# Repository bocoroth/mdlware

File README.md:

# mdlware
OSHW projects

This repo contains my OSHW (Open Source Hardware) projects, generally created using LTSpice (for sims) and KiCad (for board layout). These projects are mostly related to Eurorack synthesizers.

These projects are released under the CERN-OHL-2.0-S license, which means they are free for anyone to use or make derivatives thereof, provided derivatives remain open source (i.e., no proprietary derivatives). See the LICENSE file for more information.

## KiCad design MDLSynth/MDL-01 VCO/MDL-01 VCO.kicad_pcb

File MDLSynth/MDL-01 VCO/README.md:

# MDL-01 VCO

A tracking Voltage Controlled Oscillator

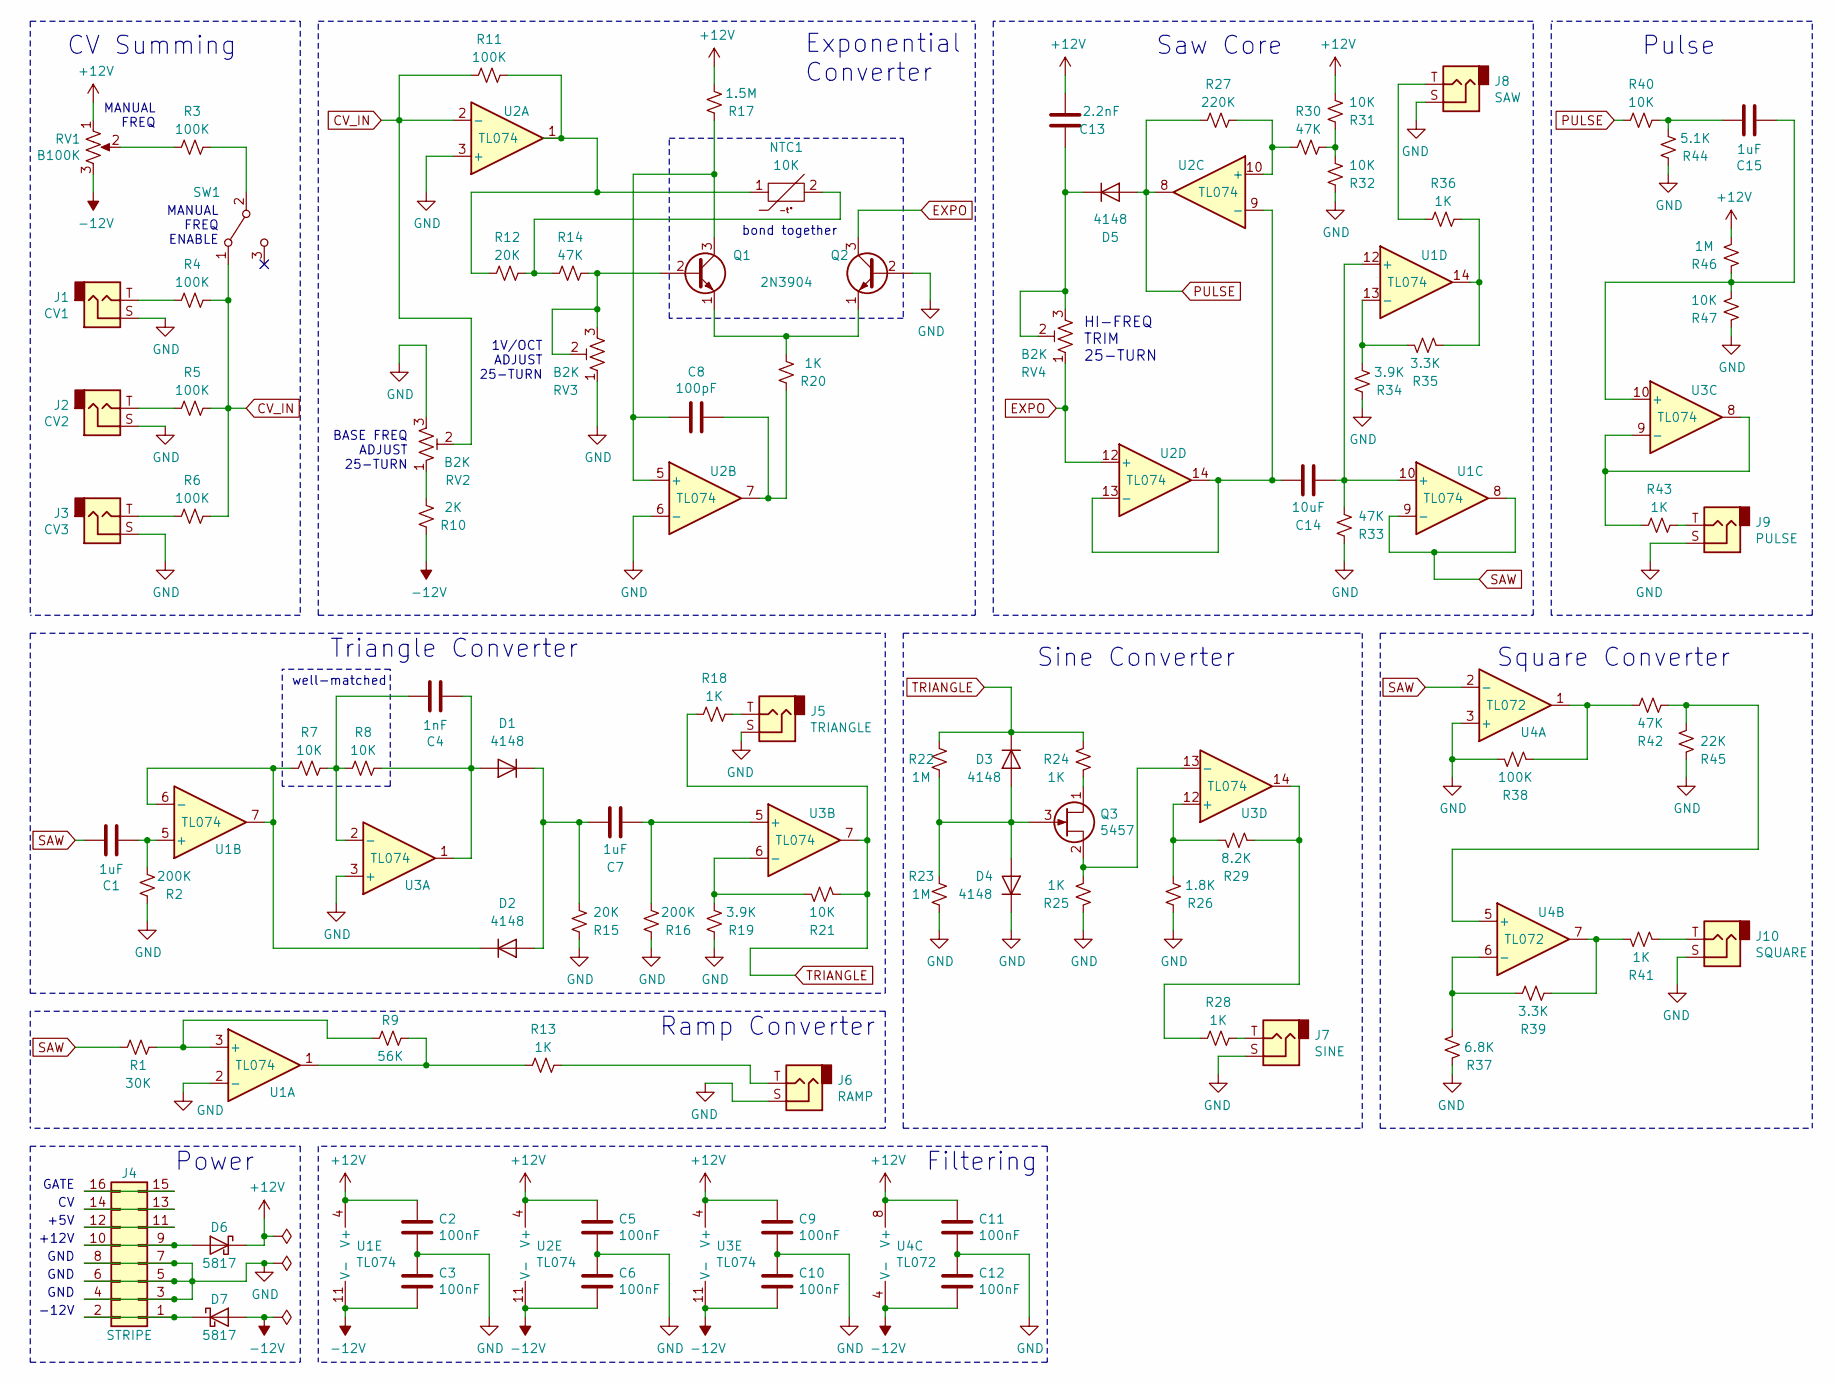
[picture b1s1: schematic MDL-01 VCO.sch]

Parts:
C1, C7, C15: 1uF; C_Elec_4x5.4; Digi-Key PCE4301CT-ND
C2, C3, C5, C6, C9, C10, C11, C12: 100nF; C_0805_2012Metric; Digi-Key 1276-2449-1-ND
C4: 1nF; C_0805_2012Metric; Digi-Key 1276-1020-1-ND
C8: 100pF; C_0805_2012Metric; Digi-Key 399-15000-1-ND
C13: 2.2nF; C_0805_2012Metric; Digi-Key 1276-2484-1-ND
C14: 10uF; C_Elec_6.3x5.4; Digi-Key PCE4294CT-ND
D1, D2, D3, D4, D5: 4148; D_MiniMELF; Digi-Key FDLL4148-D87ZCT-ND
D6, D7: 5817; D_SOD-323_HandSoldering; Digi-Key B5817WS-TPMSCT-ND
J1: CV1; Thonkiconn; Digi-Key --
J2: CV2; Thonkiconn; Digi-Key --
J3: CV3; Thonkiconn; Digi-Key --
J4: STRIPE; IDC-Header_2x08_P2.54mm_Vertical; Digi-Key S9171-ND
J5: TRIANGLE; Thonkiconn; Digi-Key --
J6: RAMP; Thonkiconn; Digi-Key --
J7: SINE; Thonkiconn; Digi-Key --
J8: SAW; Thonkiconn; Digi-Key --
J9: PULSE; Thonkiconn; Digi-Key --
J10: SQUARE; Thonkiconn; Digi-Key --
NTC1: 10K; THERM_NXRT15WB333JA1B010; Digi-Key 490-7171-ND
Q1, Q2: 2N3904; TO-92; Digi-Key 2N3904-APCT-ND
Q3: 5457; SOT-23; Digi-Key MMBF5457CT-ND
R1: 30K; R_0805_2012Metric; Digi-Key 2019-RK73H2ATTD3002FCT-ND
R2, R16: 200K; R_0805_2012Metric; Digi-Key 2019-RK73H2ATTD2003FCT-ND
R3, R4, R5, R6, R11, R38: 100K; R_0805_2012Metric; Digi-Key 13-AC0805FR-7W100KLCT-ND
R7, R8, R21, R31, R32, R40, R47: 10K; R_0805_2012Metric; Digi-Key 2019-RK73H2ATTE1002FCT-ND
R9: 56K; R_0805_2012Metric; Digi-Key 2019-RK73H2ATTD5602FCT-ND
R10: 2K; R_0805_2012Metric; Digi-Key RNCP0805FTD2K00CT-ND
R12, R15: 20K; R_0805_2012Metric; Digi-Key 2019-RK73H2ATTD2002FCT-ND
R13, R18, R20, R24, R25, R28, R36, R41, R43: 1K; R_0805_2012Metric; Digi-Key 2019-RK73H2ATTD1001FCT-ND
R14, R30, R33, R42: 47K; R_0805_2012Metric; Digi-Key 2019-RK73H2ATTD4702FCT-ND
R17: 1.5M; R_0805_2012Metric; Digi-Key 2019-RK73H2ATTD1504FCT-ND
R19, R34: 3.9K; R_0805_2012Metric; Digi-Key 2019-RK73H2ATTD3901FCT-ND
R22, R23, R46: 1M; R_0805_2012Metric; Digi-Key 2019-RK73H2ATTD1004FCT-ND
R26: 1.8K; R_0805_2012Metric; Digi-Key 2019-RK73H2ATTD1801FCT-ND
R27: 220K; R_0805_2012Metric; Digi-Key RHM220KAECT-ND
R29: 8.2K; R_0805_2012Metric; Digi-Key 2019-RK73H2ATTD8201FCT-ND
R35, R39: 3.3K; R_0805_2012Metric; Digi-Key 2019-RK73H2ATTD3R30FCT-ND
R37: 6.8K; R_0805_2012Metric; Digi-Key 2019-RK73H2ATTD6801FCT-ND
R44: 5.1K; R_0805_2012Metric; Digi-Key 2019-RK73H2ATTD5101FCT-ND
R45: 22K; R_0805_2012Metric; Digi-Key 2019-RK73H2ATTD2202FCT-ND
RV1: B100K; Potentiometer_Alpha_RD901F-40-00D_Single_Vertical; Digi-Key --
RV2, RV3, RV4: B2K; Potentiometer_Bourns_3296W_Vertical; Digi-Key 490-2880-ND
SW1: MANUAL FREQ; SW_Toggle_Blue_wSlots; Digi-Key EG2350-ND
U1, U2, U3: TL074; SOIC-14_3.9x8.7mm_P1.27mm; Digi-Key 296-TL074HIDRCT-ND
U4: TL072; SOIC-8_3.9x4.9mm_P1.27mm; Digi-Key 296-52761-1-ND

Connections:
+12V: C2.1, C5.1, C9.1, C11.1, C13.1, D6.1 (K), R17.2, R31.2, R46.2, RV1.1, U1.4 (V+), U2.4 (V+), U3.4 (V+), U4.8 (V+)
-12V: C3.2, C6.2, C10.2, C12.2, D7.2 (A), R10.1, RV1.3, U1.11 (V-), U2.11 (V-), U3.11 (V-), U4.4 (V-)
CV_IN: R4.1, R5.1, R6.1, R11.2, RV2.2, SW1.1 (A), U2.2 (-)
EXPO: Q2.3 (C), RV4.1, U2.12 (+)
GND: C2.2, C3.1, C5.2, C6.1, C9.2, C10.1, C11.2, C12.1, D4.1 (K), J1.S, J2.S, J3.S, J4.3, J4.4, J4.5, J4.6, J4.7, J4.8, J5.S, J6.S, J7.S, J8.S, J9.S, J10.S, Q2.2 (B), R2.1, R15.1, R16.1, R19.1, R23.1, R25.1, R26.1, R32.1, R33.1, R34.1, R37.2, R38.1, R44.1, R45.2, R47.1, RV2.3, RV3.1, U1.2 (-), U2.3 (+), U2.6 (-), U3.3 (+), U4.3 (+)
unnamed: C1.2, R2.2, U1.5 (+)
unnamed: C4.1, R7.1, R8.2, U3.2 (-)
unnamed: C4.2, D1.2 (A), R8.1, U3.1
unnamed: C7.1, D1.1 (K), D2.2 (A), R15.2
unnamed: C7.2, R16.2, U3.5 (+)
unnamed: C8.1, Q1.3 (C), R17.1, U2.5 (+)
unnamed: C8.2, R20.1, U2.7
unnamed: C13.2, D5.1 (K), RV4.2, RV4.3
unnamed: C14.1, U2.9 (-), U2.13 (-), U2.14
unnamed: C14.2, R33.2, U1.10 (+), U1.12 (+)
unnamed: C15.1, R40.1, R44.2
unnamed: C15.2, R46.1, R47.2, U3.10 (+)
unnamed: D2.1 (K), R7.2, U1.6 (-), U1.7
unnamed: D3.2 (A), D4.2 (A), Q3.3 (G), R22.1, R23.2
unnamed: D6.2 (A), J4.9, J4.10
unnamed: D7.1 (K), J4.1, J4.2
unnamed: J1.T, R4.2
unnamed: J2.T, R5.2
unnamed: J3.T, R6.2
unnamed: J4.11, J4.12
unnamed: J4.13, J4.14
unnamed: J4.15, J4.16
unnamed: J5.T, R18.1
unnamed: J6.T, R13.1
unnamed: J7.T, R28.1
unnamed: J8.T, R36.2
unnamed: J9.T, R43.1
unnamed: J10.T, R41.1
unnamed: NTC1.1, R11.1, R12.2, U2.1
unnamed: NTC1.2, R12.1, R14.2
unnamed: Q1.1 (E), Q2.1 (E), R20.2
unnamed: Q1.2 (B), R14.1, RV3.2, RV3.3
unnamed: Q3.1 (D), R24.1
unnamed: Q3.2 (S), R25.2, U3.13 (-)
unnamed: R1.1, R9.2, U1.3 (+)
unnamed: R3.1, SW1.2 (B)
unnamed: R3.2, RV1.2
unnamed: R10.2, RV2.1
unnamed: R9.1, R13.2, U1.1
unnamed: R19.2, R21.2, U3.6 (-)
unnamed: R26.2, R29.2, U3.12 (+)
unnamed: R27.1, R30.2, U2.10 (+)
unnamed: R28.2, R29.1, U3.14
unnamed: R30.1, R31.1, R32.2
unnamed: R34.2, R35.2, U1.13 (-)
unnamed: R35.1, R36.1, U1.14
unnamed: R37.1, R39.1, U4.6 (-)
unnamed: R38.2, R42.1, U4.1
unnamed: R39.2, R41.2, U4.7
unnamed: R42.2, R45.1, U4.5 (+)
unnamed: R43.2, U3.8, U3.9 (-)
PULSE: D5.2 (A), R27.2, R40.2, U2.8
SAW: C1.1, R1.2, U1.8, U1.9 (-), U4.2 (-)
TRIANGLE: D3.1 (K), R18.2, R21.1, R22.2, R24.2, U3.7

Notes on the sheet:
MANUAL FREQ
bond together
1V/OCT ADJUST 25-TURN
MANUAL FREQ ENABLE
CV Summing
Exponential Converter
Saw Core
HI-FREQ TRIM 25-TURN
Triangle Converter
Square Converter
Filtering
Ramp Converter
+5V
GATE
+12V
GND
-12V
BASE FREQ ADJUST 25-TURN
Pulse
well-matched
Sine Converter
Power

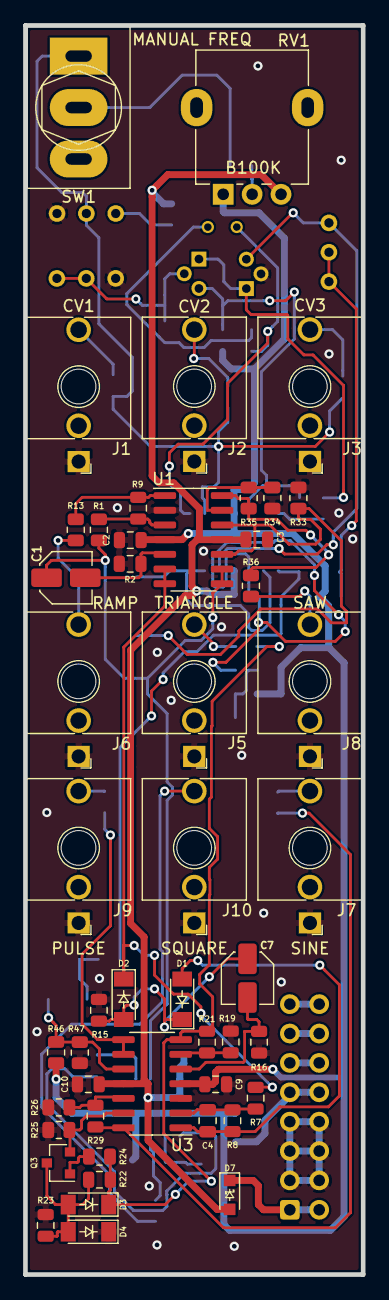
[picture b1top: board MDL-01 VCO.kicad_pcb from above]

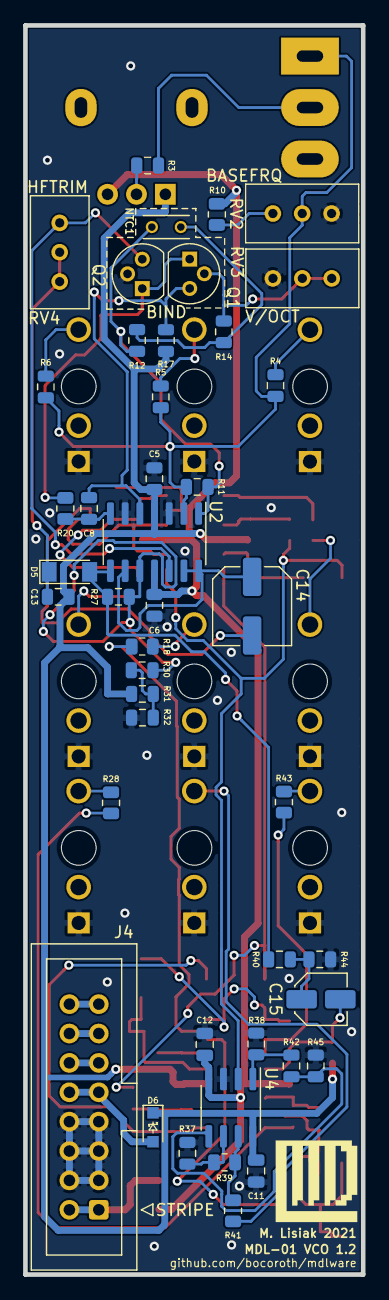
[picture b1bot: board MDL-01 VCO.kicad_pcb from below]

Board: 2 copper layers, 29.2 x 108.0 mm, 92 parts (44 on the bottom side), 59 nets.

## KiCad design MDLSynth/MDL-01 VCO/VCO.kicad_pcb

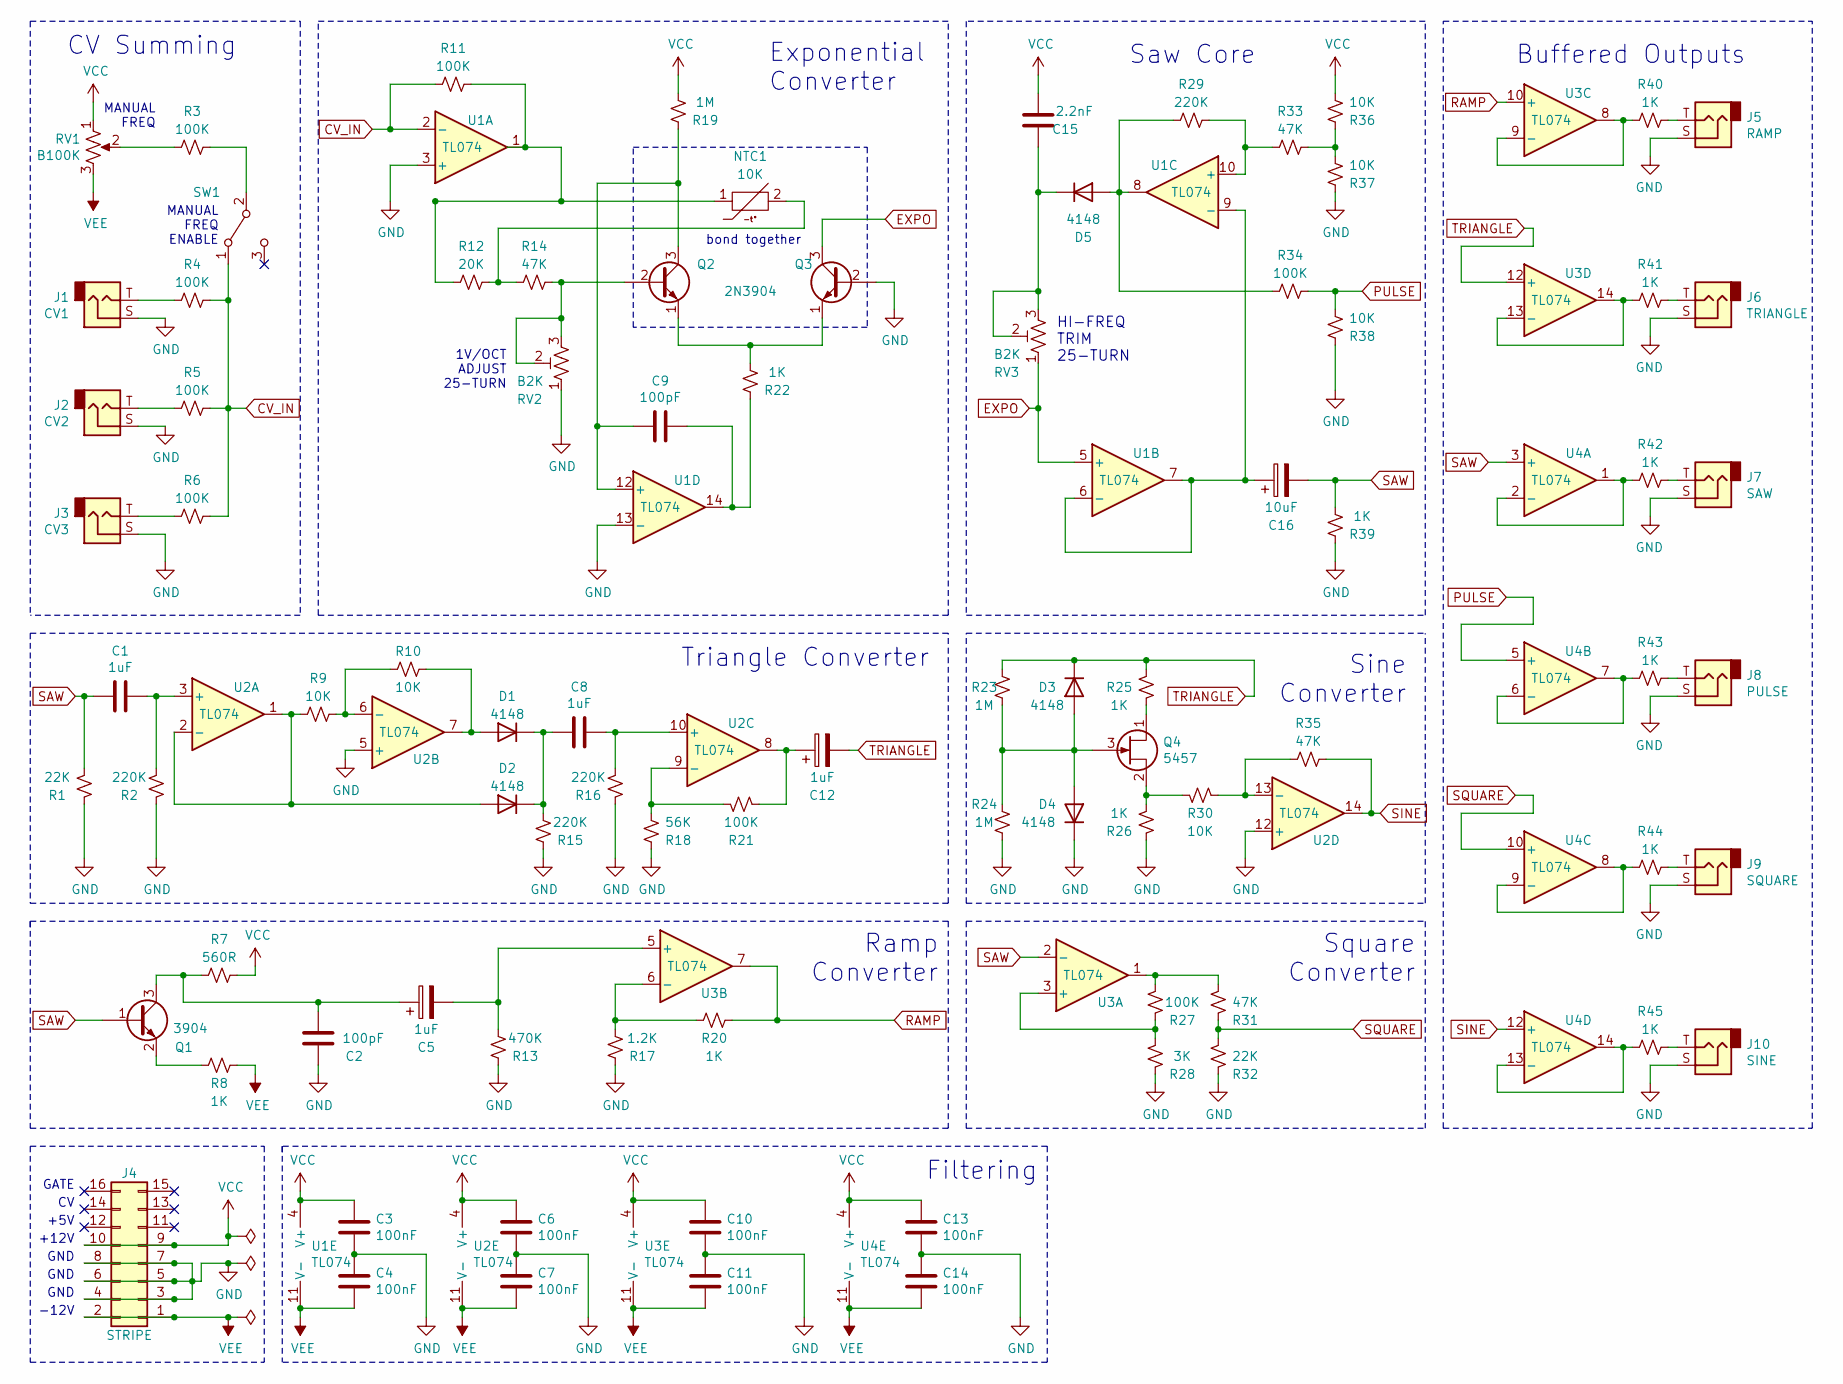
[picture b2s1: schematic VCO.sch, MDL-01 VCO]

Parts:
C1, C8: 1uF; C_1206_3216Metric; DIGIKEY 1276-3091-1-ND
C2, C9: 100pF; C_0805_2012Metric; DIGIKEY 1276-1014-1-ND
C3, C4, C6, C7, C10, C11, C13, C14: 100nF; C_0805_2012Metric; DIGIKEY 1276-1003-1-ND
C5, C12: 1uF; CP_Elec_4x5.4; DIGIKEY 732-8541-1-ND
C15: 2.2nF; C_0805_2012Metric; DIGIKEY 1276-1171-1-ND
C16: 10uF; CP_Elec_5x5.4; DIGIKEY 732-8451-1-ND
D1, D2, D3, D4, D5: 4148; D_MiniMELF; DIGIKEY FDLL4148CT-ND
J1: CV1; Thonkiconn; DIGIKEY --
J2: CV2; Thonkiconn; DIGIKEY --
J3: CV3; Thonkiconn; DIGIKEY --
J4: STRIPE; IDC-Header_2x08_P2.54mm_Vertical; DIGIKEY ED10523-ND
J5: RAMP; Thonkiconn; DIGIKEY --
J6: TRIANGLE; Thonkiconn; DIGIKEY --
J7: SAW; Thonkiconn; DIGIKEY --
J8: PULSE; Thonkiconn; DIGIKEY --
J9: SQUARE; Thonkiconn; DIGIKEY --
J10: SINE; Thonkiconn; DIGIKEY --
NTC1: 10K; THERM_NXRT15WB333JA1B010; DIGIKEY 490-18143-1-ND
Q1: 3904; SOT-23; DIGIKEY MMBT3904TPMSCT-ND
Q2, Q3: 2N3904; TO-92; DIGIKEY 2N3904D26ZCT-ND
Q4: 5457; SOT-23; DIGIKEY MMBF5457CT-ND
R1, R32: 22K; R_0805_2012Metric; DIGIKEY RMCF0805FT22K0CT-ND
R2, R15, R16, R29: 220K; R_0805_2012Metric; DIGIKEY RMCF0805FT220KCT-ND
R3, R4, R5, R6, R11, R21, R27, R34: 100K; R_0805_2012Metric; DIGIKEY RMCF0805FT100KCT-ND
R7: 560R; R_1206_3216Metric; DIGIKEY RMCF1206JT560RCT-ND
R8, R20, R22, R25, R26, R39, R40, R41, R42, R43, R44, R45: 1K; R_1206_3216Metric; DIGIKEY RMCF1206FT1K00CT-ND
R9, R10, R30, R36, R37, R38: 10K; R_0805_2012Metric; DIGIKEY RMCF0805FT10K0CT-ND
R12: 20K; R_0805_2012Metric; DIGIKEY RMCF0805FT20K0CT-ND
R13: 470K; R_0805_2012Metric; DIGIKEY 738-RMCF0805FT470KCT-ND
R14, R31, R33, R35: 47K; R_0805_2012Metric; DIGIKEY RMCF0805FT47K0CT-ND
R17: 1.2K; R_0805_2012Metric; DIGIKEY RMCF0805FT1K20CT-ND
R18: 56K; R_0805_2012Metric; DIGIKEY RMCF0805FT56K0CT-ND
R19, R23, R24: 1M; R_0805_2012Metric; DIGIKEY RMCF0805FG1M00CT-ND
R28: 3K; R_0805_2012Metric; DIGIKEY RMCF0805FT3K00CT-ND
RV1: B100K; Potentiometer_Alpha_RD901F-40-00D_Single_Vertical; DIGIKEY --
RV2, RV3: B2K; Potentiometer_Bourns_3296W_Vertical; DIGIKEY PV36W202C01B00
SW1: MANUAL FREQ; SW_Toggle_Blue_wSlots; DIGIKEY EG2350-ND
U1, U2: TL074; SOIC-14_3.9x8.7mm_P1.27mm; DIGIKEY 296-1283-1-ND
U3, U4: TL074; SOIC-14_3.9x8.7mm_P1.27mm; DIGIKEY 296-1282-1-ND

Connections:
CV_IN: R4.1, R5.1, R6.1, R11.2, SW1.1 (A), U1.2 (-)
EXPO: Q3.3 (C), RV3.1, U1.5 (+)
GND: C2.2, C3.2, C4.1, C6.2, C7.1, C10.2, C11.1, C13.2, C14.1, D4.1 (K), J1.S, J2.S, J3.S, J4.3, J4.4, J4.5, J4.6, J4.7, J4.8, J5.S, J6.S, J7.S, J8.S, J9.S, J10.S, Q3.2 (B), R1.1, R2.1, R13.1, R15.1, R16.1, R17.1, R18.1, R24.1, R26.1, R28.2, R32.2, R37.1, R38.1, R39.1, RV2.1, U1.3 (+), U1.13 (-), U2.5 (+), U2.12 (+)
unnamed: C1.2, R2.2, U2.3 (+)
unnamed: C2.1, C5.1, Q1.3 (C), R7.2
unnamed: C5.2, R13.2, U3.5 (+)
unnamed: C8.1, D1.1 (K), D2.1 (K), R15.2
unnamed: C8.2, R16.2, U2.10 (+)
unnamed: C9.1, Q2.3 (C), R19.1, U1.12 (+)
unnamed: C9.2, R22.1, U1.14
unnamed: C12.1, R21.1, U2.8
unnamed: C15.2, D5.1 (K), RV3.2, RV3.3
unnamed: C16.1, U1.6 (-), U1.7, U1.9 (-)
unnamed: D1.2 (A), R10.1, U2.7
unnamed: D2.2 (A), R9.2, U2.1, U2.2 (-)
unnamed: D3.2 (A), D4.2 (A), Q4.3 (G), R23.1, R24.2
unnamed: D5.2 (A), R29.2, R34.2, U1.8
unnamed: J1.T, R4.2
unnamed: J2.T, R5.2
unnamed: J3.T, R6.2
unnamed: J5.T, R40.1
unnamed: J6.T, R41.1
unnamed: J7.T, R42.1
unnamed: J8.T, R43.1
unnamed: J9.T, R44.1
unnamed: J10.T, R45.1
unnamed: NTC1.1, R11.1, R12.2, U1.1
unnamed: NTC1.2, R12.1, R14.2
unnamed: Q1.2 (E), R8.2
unnamed: Q2.1 (E), Q3.1 (E), R22.2
unnamed: Q2.2 (B), R14.1, RV2.2, RV2.3
unnamed: Q4.1 (D), R25.1
unnamed: Q4.2 (S), R26.2, R30.2
unnamed: R3.1, SW1.2 (B)
unnamed: R3.2, RV1.2
unnamed: R9.1, R10.2, U2.6 (-)
unnamed: R17.2, R20.2, U3.6 (-)
unnamed: R18.2, R21.2, U2.9 (-)
unnamed: R27.1, R31.1, U3.1
unnamed: R27.2, R28.1, U3.3 (+)
unnamed: R29.1, R33.2, U1.10 (+)
unnamed: R30.1, R35.2, U2.13 (-)
unnamed: R33.1, R36.1, R37.2
unnamed: R40.2, U3.8, U3.9 (-)
unnamed: R41.2, U3.13 (-), U3.14
unnamed: R42.2, U4.1, U4.2 (-)
unnamed: R43.2, U4.6 (-), U4.7
unnamed: R44.2, U4.8, U4.9 (-)
unnamed: R45.2, U4.13 (-), U4.14
PULSE: R34.1, R38.2, U4.5 (+)
RAMP: R20.1, U3.7, U3.10 (+)
SAW: C1.1, C16.2, Q1.1 (B), R1.2, R39.2, U3.2 (-), U4.3 (+)
SINE: R35.1, U2.14, U4.12 (+)
SQUARE: R31.2, R32.1, U4.10 (+)
TRIANGLE: C12.2, D3.1 (K), R23.2, R25.2, U3.12 (+)
VCC: C3.1, C6.1, C10.1, C13.1, C15.1, J4.9, J4.10, R7.1, R19.2, R36.2, RV1.1, U1.4 (V+), U2.4 (V+), U3.4 (V+), U4.4 (V+)
VEE: C4.2, C7.2, C11.2, C14.2, J4.1, J4.2, R8.1, RV1.3, U1.11 (V-), U2.11 (V-), U3.11 (V-), U4.11 (V-)

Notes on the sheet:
MANUAL FREQ
bond together
1V/OCT ADJUST 25-TURN
MANUAL FREQ ENABLE
CV Summing
Exponential Converter
Saw Core
HI-FREQ TRIM 25-TURN
Triangle Converter
Sine Converter
Square Converter
Filtering
Ramp Converter
Buffered Outputs
+5V
GATE
+12V
GND
-12V

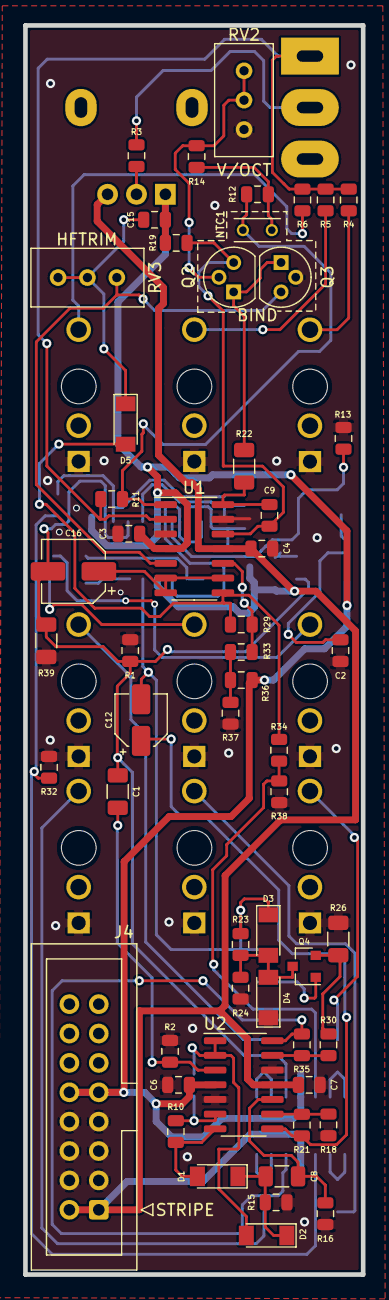
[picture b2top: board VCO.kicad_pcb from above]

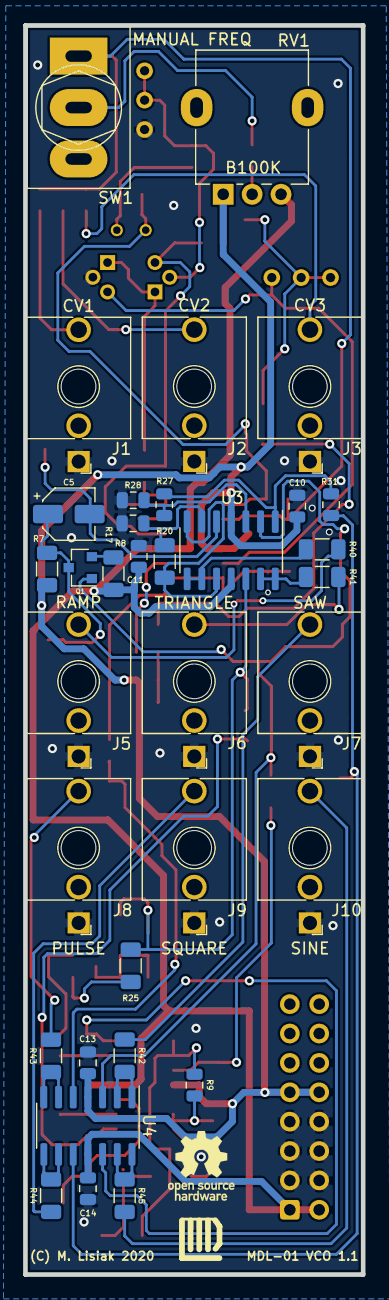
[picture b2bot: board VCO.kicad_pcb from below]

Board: 2 copper layers, 29.2 x 108.0 mm, 89 parts (34 on the bottom side), 57 nets.

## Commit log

2020-10-02 Add gitignore and license
2020-10-02 VCO initial version
2021-04-27 VCO v1.2
2021-04-27 update libraries
2021-04-27 codebase cleanup
2021-04-27 more cleanup

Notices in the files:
MDLSynth/MDL-01 VCO/MDL-01 VCO.kicad_pcb:
Copyright (C) 2020 Matt Lisiak
LICENSE: CERN-OHL-S (https://ohwr.org/cern_ohl_s_v2.txt)
MDLSynth/MDL-01 VCO/MDL-01 VCO.sch:
Copyright (C) 2020, 2021 Matt Lisiak
